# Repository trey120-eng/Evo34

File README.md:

* This is the Evo34 its designed using ergogen and kicad.

i designed it for a 8th grade project and i decided to open source it
The evo34 uses zmk frimware with zmk studio support 
also there is a unibody version which [here](https://shield-wizard.genteure.workers.dev/)

1) it uses a NiceNanoV2 (i used a clone for cost saving)
2) klplame keycaps made by braindefender
3) and the reset button, power switch, and battery are from typeractive 

> [!WARNING]
> This keyboard has muiltiple problems.
I will try to improve it but actively there are flaws with my design such as:

* The case needs a lot of improvement and adjustments
* pcb needs improvments but fully working
* and this is a repo just for the files and parts no asemably guide at this monment

* since this version i have fixed the reset button so it will work mine didnt so its desoldered

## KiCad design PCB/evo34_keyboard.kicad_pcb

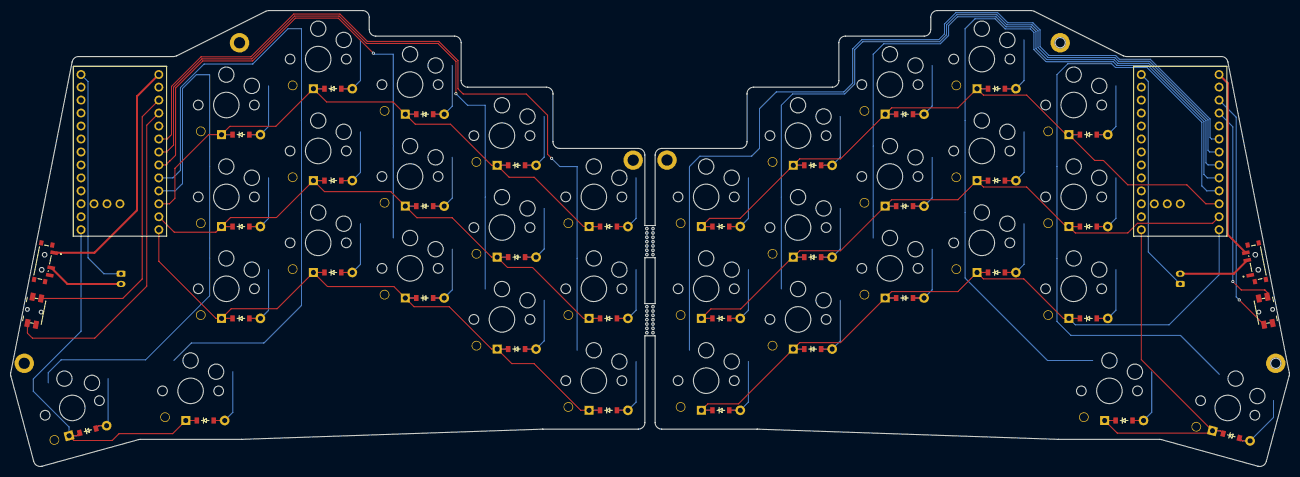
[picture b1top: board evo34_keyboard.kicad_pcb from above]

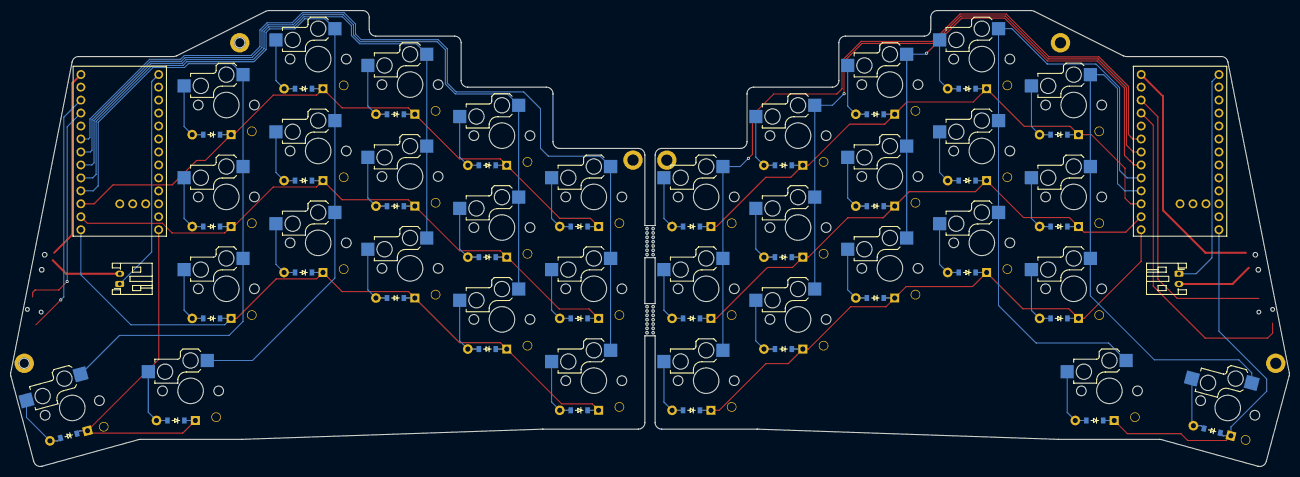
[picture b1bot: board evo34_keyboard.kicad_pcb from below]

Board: 2 copper layers, 250.5 x 89.3 mm, 70 parts (34 on the bottom side), 52 nets.

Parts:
D1, D2, D3, D4, D5, D6, D7, D8, D9, D10, D11, D12, D13, D14, D15, D16, D17, D18, D19, D20, D21, D22, D23, D24, D25, D26, D27, D28, D29, D30, D31, D32, D33, D34: ComboDiode
S1, S2, S3, S4, S5, S6, S7, S8, S9, S10, S11, S12, S13, S14, S15, S16, S17, S18, S19, S20, S21, S22, S23, S24, S25, S26, S27, S28, S29, S30, S31, S32, S33, S34: switch_choc_v1_v2
U1, U1#2: Nice_Nano_V2_clone

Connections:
L_D9: D16.1, D17.1, U1#2.13
L_D10: D1.1, D4.1, D7.1, D10.1, D13.1, U1#2.14
L_D14: D3.1, D6.1, D9.1, D12.1, D15.1, U1#2.16
L_D15: S13.1, S14.1, S15.1, S17.1, U1#2.17
L_D16: D2.1, D5.1, D8.1, D11.1, D14.1, U1#2.15
L_D18: S10.1, S11.1, S12.1, S16.1, U1#2.18
L_D19: S7.1, S8.1, S9.1, U1#2.19
L_D20: S4.1, S5.1, S6.1, U1#2.20
L_D21: S1.1, S2.1, S3.1, U1#2.21
L_index_bottom: D10.2, S10.2
L_index_home: D11.2, S11.2
L_index_top: D12.2, S12.2
L_inner_bottom: D13.2, S13.2
L_inner_home: D14.2, S14.2
L_inner_top: D15.2, S15.2
L_middle_bottom: D7.2, S7.2
L_middle_home: D8.2, S8.2
L_middle_top: D9.2, S9.2
L_pinky_bottom: D1.2, S1.2
L_pinky_home: D2.2, S2.2
L_pinky_top: D3.2, S3.2
L_ring_bottom: D4.2, S4.2
L_ring_home: D5.2, S5.2
L_ring_top: D6.2, S6.2
L_thumbfan_default: D16.2, S16.2
L_thumbfan_near: D17.2, S17.2
R_D9: D33.1, D34.1, U1.13
R_D10: D18.1, D21.1, D24.1, D27.1, D30.1, U1.14
R_D14: D20.1, D23.1, D26.1, D29.1, D32.1, U1.16
R_D15: S30.1, S31.1, S32.1, S34.1, U1.17
R_D16: D19.1, D22.1, D25.1, D28.1, D31.1, U1.15
R_D18: S27.1, S28.1, S29.1, S33.1, U1.18
R_D19: S24.1, S25.1, S26.1, U1.19
R_D20: S21.1, S22.1, S23.1, U1.20
R_D21: S18.1, S19.1, S20.1, U1.21
R_index_bottom: D27.2, S27.2
R_index_home: D28.2, S28.2
R_index_top: D29.2, S29.2
R_inner_bottom: D30.2, S30.2
R_inner_home: D31.2, S31.2
R_inner_top: D32.2, S32.2
R_middle_bottom: D24.2, S24.2
R_middle_home: D25.2, S25.2
R_middle_top: D26.2, S26.2
R_pinky_bottom: D18.2, S18.2
R_pinky_home: D19.2, S19.2
R_pinky_top: D20.2, S20.2
R_ring_bottom: D21.2, S21.2
R_ring_home: D22.2, S22.2
R_ring_top: D23.2, S23.2
R_thumbfan_default: D33.2, S33.2
R_thumbfan_near: D34.2, S34.2

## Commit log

2026-03-01 Fix formatting of warning section in README
2026-03-01 Fix typos and enhance README content
    Corrected typos and improved clarity in the README.
2026-03-01 Revise README introduction and fix formatting
    Updated introduction and formatting in README.
2026-03-01 Enhance warning section in README
    Updated warning section with red color formatting.
2026-03-01 Fix warning header formatting in README
    Corrected formatting of warning in README.
2026-03-01 Update README with additional notes on improvements
    Added a note about battery reporting and PCB improvements.
2026-03-01 Clean up README.md by removing battery reporting note
    Remove redundant battery reporting issue mention.
2026-03-01 Fix typo in PCB description
    Corrected a typographical error in the README.
2026-03-01 Fix warning section formatting and spelling errors
    Corrected formatting and spelling in README.
2026-03-01 Fix spelling and formatting issues in README
    Corrected spelling errors and improved formatting in the warning section.
2026-03-01 Fix formatting issues in README.md
2026-03-01 Fix spelling and clarity issues in README
    Corrected spelling errors and improved clarity in the README.
2026-03-01 Revise README introduction and note design flaws
    Condensed introduction and highlighted design issues.
2026-03-01 Update README to specify repo purpose
    Clarify the purpose of the repository in the README.
2026-03-01 Fix formatting and clarify warning in README
    Corrected formatting and improved clarity of warnings.
2026-03-01 Fix typo in assembly guide note
    Corrected a typo in the README regarding assembly guidance.
2026-03-01 Fix formatting in README for clarity
2026-03-01 Fix formatting in README.md
    Corrected formatting and improved readability of the project description.
2026-03-01 Fix formatting in README description
2026-03-01 Fix typo in README.md for clarity
2026-03-01 Enhance README with project details and warnings
    Updated README to include details about firmware, keycaps, and components used. Added a warning about existing design flaws.
2026-03-01 Fix formatting and improve README content
